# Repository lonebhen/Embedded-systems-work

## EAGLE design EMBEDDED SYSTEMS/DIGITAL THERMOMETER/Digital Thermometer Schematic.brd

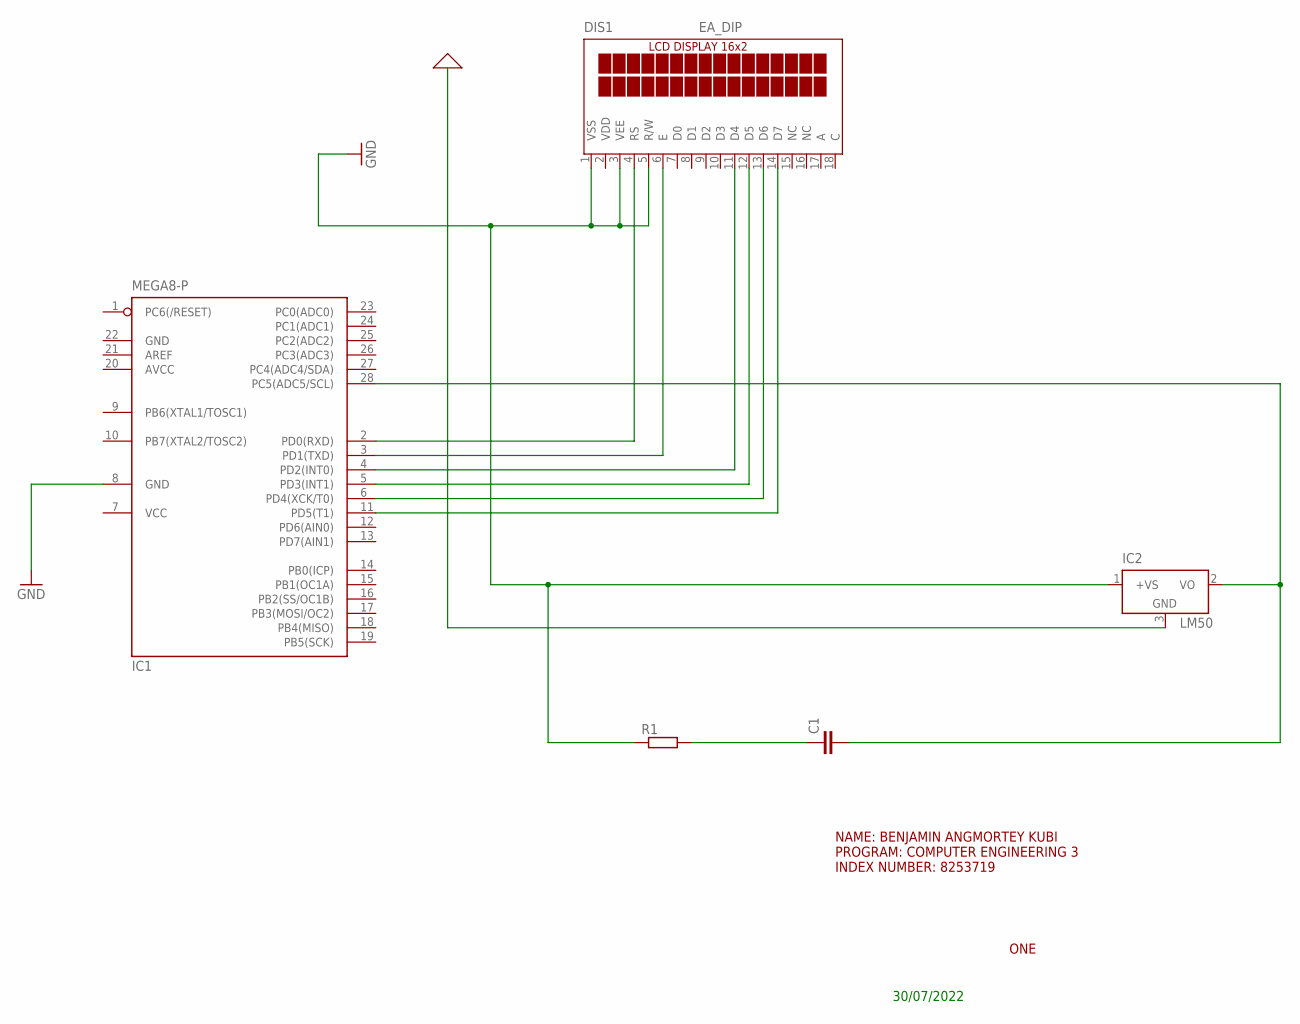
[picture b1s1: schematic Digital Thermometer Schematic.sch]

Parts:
C1: C-EU025-024X044; C025-024X044
DIS1: EA_DIP
IC1: MEGA8-P; DIL28-3
IC2: LM50; SOT23
R1: R-EU_0207/10; 0207/10

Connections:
0: IC2.3 (GND)
AVCC: IC1.20 (AVCC)
GND: DIS1.1 (VSS), DIS1.3 (VEE), DIS1.5 (R/W), IC1.8 (GND), IC1.22 (GND), IC2.1 (+VS), R1.1
unnamed: DIS1.4 (RS), IC1.2 (PD0(RXD))
unnamed: DIS1.6 (E), IC1.3 (PD1(TXD))
unnamed: DIS1.11 (D4), IC1.4 (PD2(INT0))
unnamed: DIS1.12 (D5), IC1.5 (PD3(INT1))
unnamed: DIS1.13 (D6), IC1.6 (PD4(XCK/T0))
unnamed: DIS1.14 (D7), IC1.11 (PD5(T1))
unnamed: C1.2, IC1.28 (PC5(ADC5/SCL)), IC2.2 (VO)
unnamed: C1.1, R1.2
VCC: IC1.7 (VCC)
VDD: DIS1.2 (VDD)

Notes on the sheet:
NAME: BENJAMIN ANGMORTEY KUBI PROGRAM: COMPUTER ENGINEERING 3 INDEX NUMBER: 8253719
ONE
30/07/2022

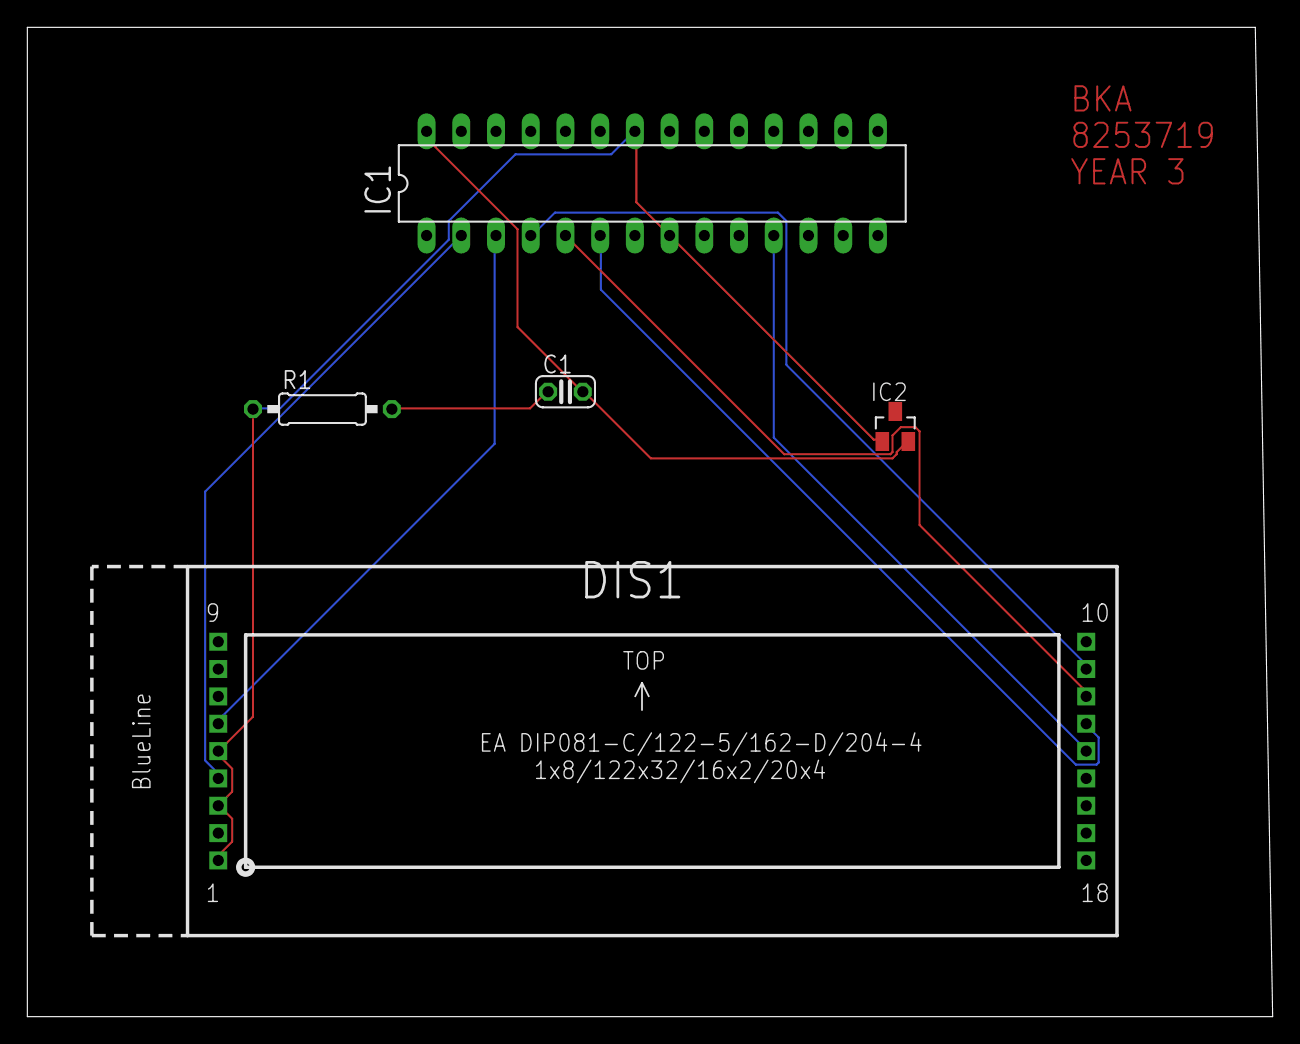
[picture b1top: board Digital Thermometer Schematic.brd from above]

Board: 2 copper layers, 91.1 x 72.4 mm, 5 parts (0 on the bottom side), 9 nets.

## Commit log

2023-03-26 embedded systems
2023-03-26 embedded systems design
